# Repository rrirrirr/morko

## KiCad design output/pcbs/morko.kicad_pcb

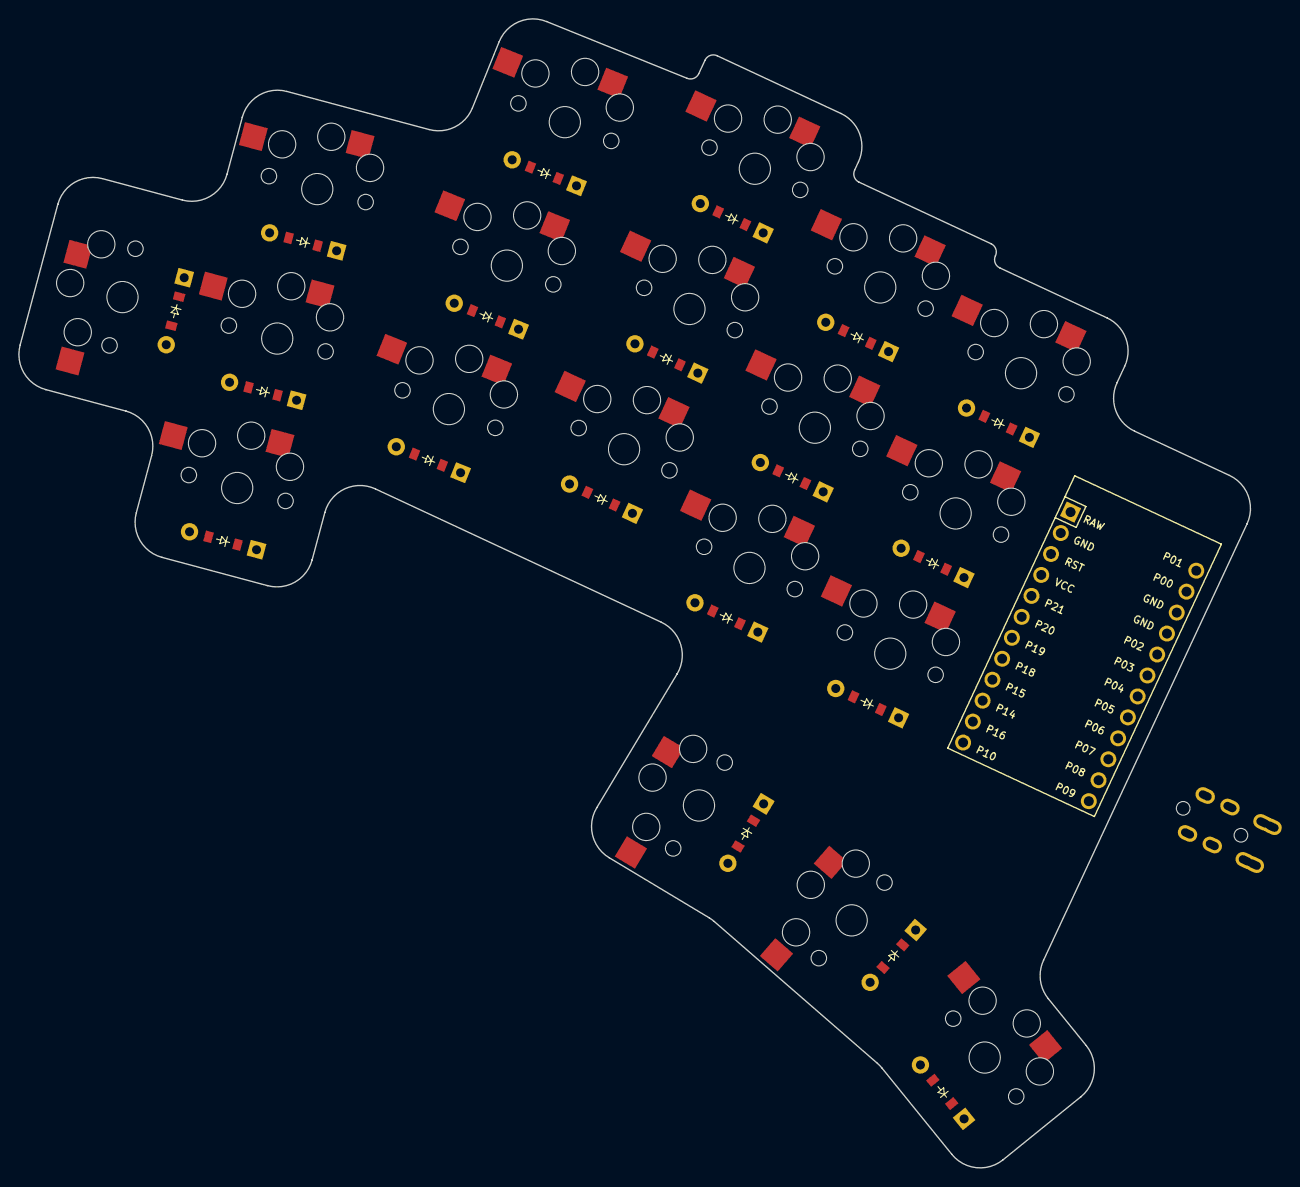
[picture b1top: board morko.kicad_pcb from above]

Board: 2 copper layers, 135.3 x 126.2 mm, 40 parts (0 on the bottom side), 32 nets, no tracks yet.

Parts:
D1, D2, D3, D4, D5, D6, D7, D8, D9, D10, D11, D12, D13, D14, D15, D16, D17, D18, D19: ComboDiode
MCU1: ProMicro
S1, S2, S3, S4, S5, S6, S7, S8, S9, S10, S11, S12, S13, S14, S15, S16, S17, S18, S19: PG1350
TRRS1: TRRS-PJ-320A-dual

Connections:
GND: MCU1.2, MCU1.15, MCU1.16, TRRS1.1, TRRS1.2
P2: D17.1, D18.1, D19.1, MCU1.17, TRRS1.3
P4: MCU1.19, S14.1, S15.1, S16.1
P5: MCU1.20, S11.1, S12.1, S13.1
P7: MCU1.22, S8.1, S9.1, S10.1
P8: MCU1.23, S5.1, S6.1, S7.1
P9: MCU1.24, S2.1, S3.1, S4.1
P10: MCU1.12, S1.1
P11: D2.1, D5.1, D8.1, D11.1, D14.1
P12: D1.1, D3.1, D6.1, D9.1, D12.1, D15.1
P13: D4.1, D7.1, D10.1, D13.1, D16.1
P19: MCU1.7, S17.1, S18.1, S19.1
VCC: MCU1.4, TRRS1.4
far_thumb: D19.2, S19.2
home_thumb: D18.2, S18.2
index_bottom: D11.2, S11.2
index_home: D12.2, S12.2
index_top: D13.2, S13.2
inner_bottom: D14.2, S14.2
inner_home: D15.2, S15.2
inner_top: D16.2, S16.2
middle_bottom: D8.2, S8.2
middle_home: D9.2, S9.2
middle_top: D10.2, S10.2
near_thumb: D17.2, S17.2
outer_home: D1.2, S1.2
pinky_bottom: D2.2, S2.2
pinky_home: D3.2, S3.2
pinky_top: D4.2, S4.2
ring_bottom: D5.2, S5.2
ring_home: D6.2, S6.2
ring_top: D7.2, S7.2

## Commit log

2023-03-26 add nice nano and promicro pretty footprints
2023-05-12 Direct pin version with fewer buttons
